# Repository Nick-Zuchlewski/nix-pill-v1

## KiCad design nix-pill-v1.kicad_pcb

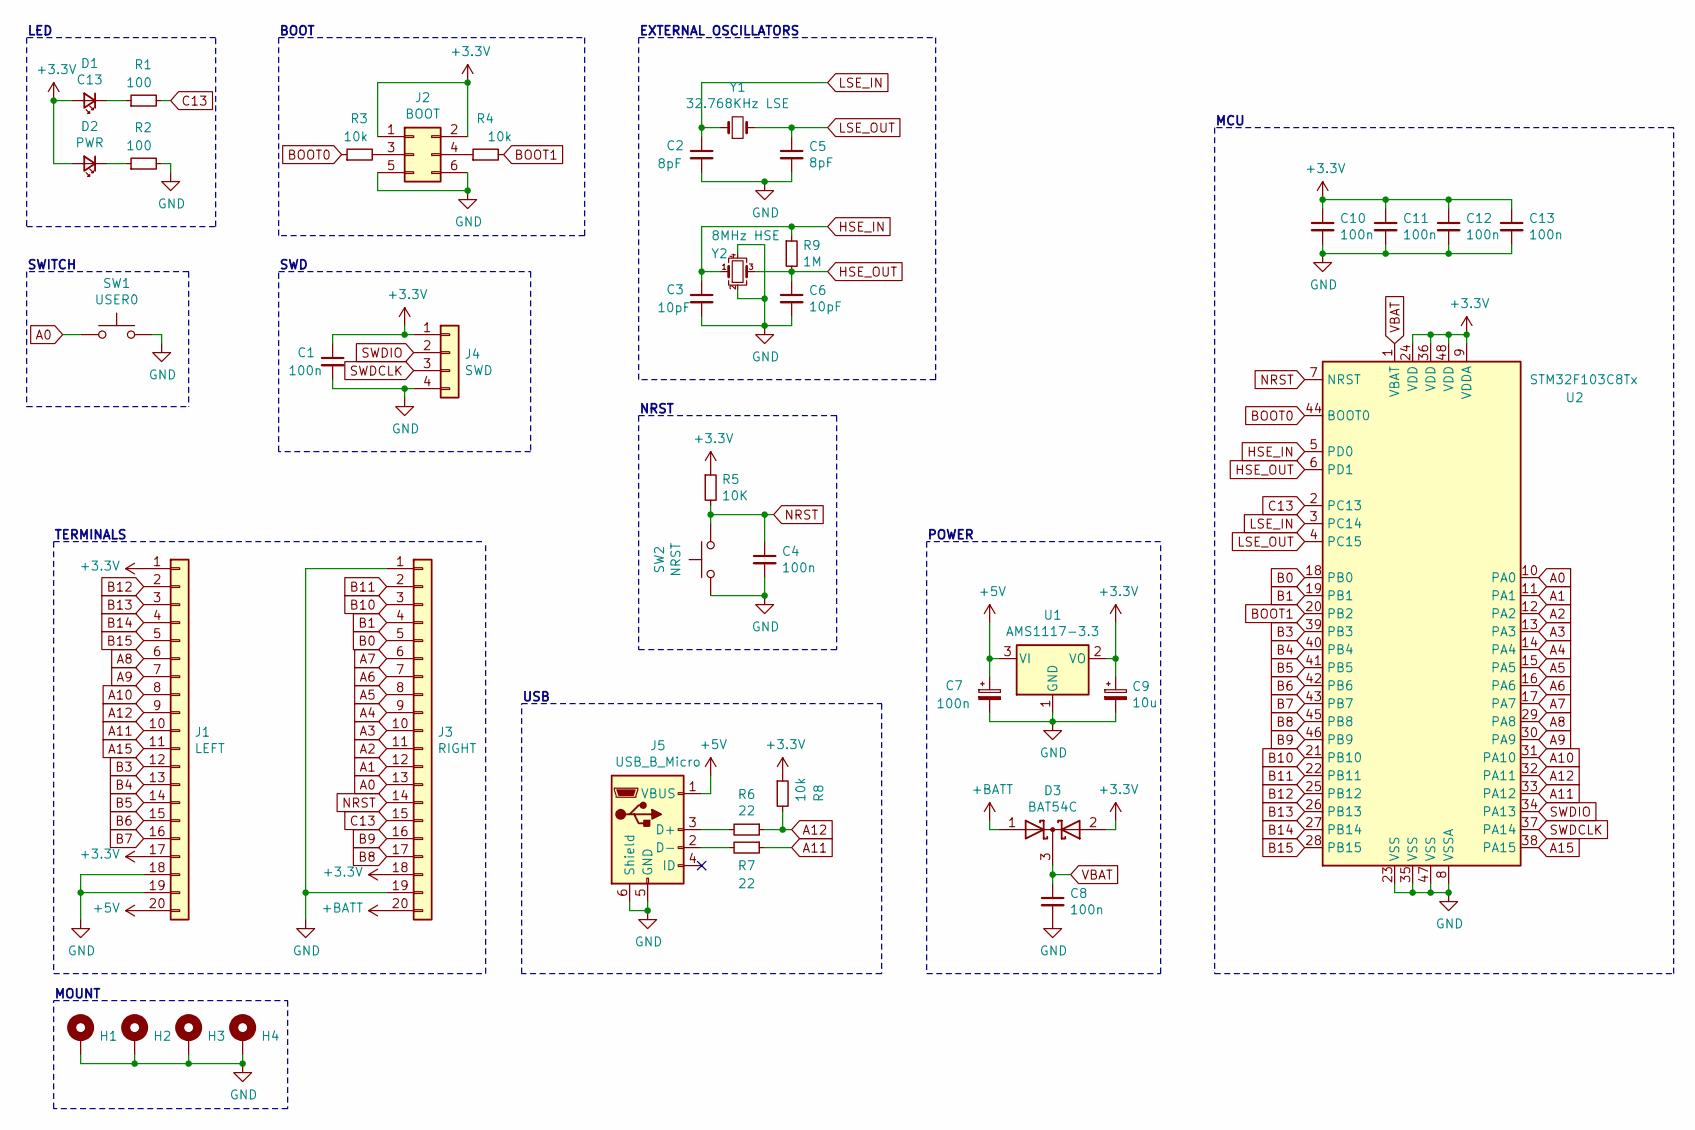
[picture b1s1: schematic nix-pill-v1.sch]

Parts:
C1, C4, C8, C10, C11, C12, C13: 100n; C_0603_1608Metric
C2, C5: 8pF; C_0603_1608Metric
C3, C6: 10pF; C_0603_1608Metric
C7: 100n; CP_Elec_4x3
C9: 10u; CP_Elec_4x3
D1: C13; LED_0603_1608Metric
D2: PWR; LED_0603_1608Metric
D3: BAT54C; SOT-23
H1, H2, H3, H4: MountingHole_Pad; MountingHole_4.3mm_M4_Pad_Via
J1: LEFT; PinHeader_1x20_P2.54mm_Vertical
J2: BOOT; PinHeader_2x03_P2.54mm_Vertical
J3: RIGHT; PinHeader_1x20_P2.54mm_Vertical
J4: SWD; PinHeader_1x04_P2.54mm_Horizontal
J5: USB_B_Micro; USB_Micro-B_Amphenol_10103594-0001LF_Horizontal
R1, R2: 100; R_0603_1608Metric
R3, R4, R8: 10k; R_0603_1608Metric
R5: 10K; R_0603_1608Metric
R6, R7: 22; R_0603_1608Metric
R9: 1M; R_0603_1608Metric
SW1: USER0; SW_SPST_TL3305A
SW2: NRST; SW_SPST_TL3305A
U1: AMS1117-3.3; SOT-223-3_TabPin2
U2: STM32F103C8Tx; LQFP-48_7x7mm_P0.5mm
Y1: 32.768KHz LSE; Crystal_SMD_MicroCrystal_CC5V-T1A-2Pin_4.1x1.5mm
Y2: 8MHz HSE; Crystal_SMD_3225-4Pin_3.2x2.5mm

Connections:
+3V3: C1.1, C9.1, C10.1, C11.1, C12.1, C13.1, D1.2 (A), D2.2 (A), D3.2 (A), J1.1, J1.17, J2.1, J2.2, J3.18, J4.1, R5.1, R8.1, U1.2 (VO), U2.9 (VDDA), U2.24 (VDD), U2.36 (VDD), U2.48 (VDD)
+5V: C7.1, J1.20, J5.1 (VBUS), U1.3 (VI)
+BATT: D3.1 (A), J3.20
A0: J3.13, SW1.1, U2.10 (PA0)
A1: J3.12, U2.11 (PA1)
A2: J3.11, U2.12 (PA2)
A3: J3.10, U2.13 (PA3)
A4: J3.9, U2.14 (PA4)
A5: J3.8, U2.15 (PA5)
A6: J3.7, U2.16 (PA6)
A7: J3.6, U2.17 (PA7)
A8: J1.6, U2.29 (PA8)
A9: J1.7, U2.30 (PA9)
A10: J1.8, U2.31 (PA10)
A11: J1.10, R7.1, U2.33 (PA12)
A12: J1.9, R6.1, R8.2, U2.32 (PA11)
A15: J1.11, U2.38 (PA15)
B0: J3.5, U2.18 (PB0)
B1: J3.4, U2.19 (PB1)
B3: J1.12, U2.39 (PB3)
B4: J1.13, U2.40 (PB4)
B5: J1.14, U2.41 (PB5)
B6: J1.15, U2.42 (PB6)
B7: J1.16, U2.43 (PB7)
B8: J3.17, U2.45 (PB8)
B9: J3.16, U2.46 (PB9)
B10: J3.3, U2.21 (PB10)
B11: J3.2, U2.22 (PB11)
B12: J1.2, U2.25 (PB12)
B13: J1.3, U2.26 (PB13)
B14: J1.4, U2.27 (PB14)
B15: J1.5, U2.28 (PB15)
BOOT0: R3.1, U2.44 (BOOT0)
BOOT1: R4.2, U2.20 (PB2)
C13: J3.15, R1.2, U2.2 (PC13)
GND: C1.2, C2.2, C3.2, C4.2, C5.2, C6.2, C7.2, C8.2, C9.2, C10.2, C11.2, C12.2, C13.2, H1.1, H2.1, H3.1, H4.1, J1.18, J1.19, J2.5, J2.6, J3.1, J3.19, J4.4, J5.5 (GND), J5.6 (Shield), R2.2, SW1.2, SW2.1, U1.1 (GND), U2.8 (VSSA), U2.23 (VSS), U2.35 (VSS), U2.47 (VSS), Y2.2, Y2.4
HSE_IN: C3.1, R9.1, U2.5 (PD0), Y2.1
HSE_OUT: C6.1, R9.2, U2.6 (PD1), Y2.3
LSE_IN: C2.1, U2.3 (PC14), Y1.1
LSE_OUT: C5.1, U2.4 (PC15), Y1.2
NRST: C4.1, J3.14, R5.2, SW2.2, U2.7 (NRST)
unnamed: D1.1 (K), R1.1
unnamed: D2.1 (K), R2.1
unnamed: J2.3, R3.2
unnamed: J2.4, R4.1
unnamed: J5.2 (D-), R7.2
unnamed: J5.3 (D+), R6.2
SWDCLK: J4.3, U2.37 (PA14)
SWDIO: J4.2, U2.34 (PA13)
VBAT: C8.1, D3.3 (K), U2.1 (VBAT)

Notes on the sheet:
POWER
SWD
NRST
EXTERNAL OSCILLATORS
TERMINALS
BOOT
USB
SWITCH
LED
MCU
MOUNT

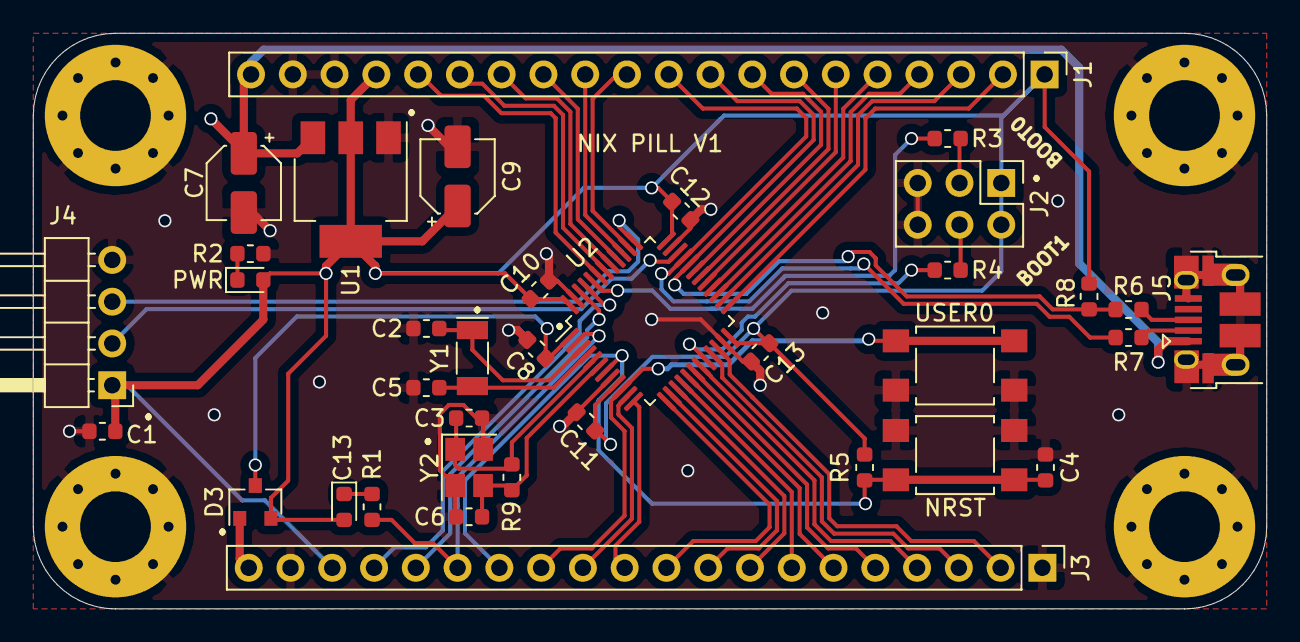
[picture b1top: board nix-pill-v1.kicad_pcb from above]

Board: 2 copper layers, 75.0 x 35.0 mm, 40 parts (0 on the bottom side), 50 nets.

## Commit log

2021-01-25 init commit
2021-01-26 Started adding data sheets Started the BOM Calculated the LED limiting R
2021-01-27 Added more data sheets and updated BOM
2021-01-28 BOM completed. Ordering PCB and parts
2021-01-29 Testing the GH actions
2021-01-29 Adding own config with filter
2021-01-29 Updated workflow for anything
2021-01-29 Set the board clearance to match board house.
2021-01-29 It helps to update the action...
2021-01-29 its docs not docs. Get it right.
2021-02-02 expirimenting with gerber generation
2021-02-02 removed gerbers update the action for gerbers, docs, and bom
